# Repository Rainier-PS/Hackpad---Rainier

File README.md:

# Hackpad-Rainier

Hackpad-Rainier is a small 3x3 macropad featuring an encoder, OLED display, LED backlight, and various keymap layers. It is constructed using KMK firmware and the Seeed XIAO RP2040. It is designed to facilitate shortcuts, media management, number entry, and visual feedback for different layers.

## Features

- 3×3 key configuration (9 physical buttons)
- EC11 rotary encoder that includes a push button
- Layer switching through encoder press or key combinations
- OLED display for showing layers and modes
- SK6812 MINI-E LEDs backlight with several brightness settings
- KMK firmware 
- Custom-designed PCB (2-layer) and a 3D-printed case

## Visual Overview

### Assembled Hackpad

>In accordance with the submission requirements, the interior of both the top and bottom parts of the case are branded with my name.

### Schematic

### PCB Layout

## Layer Configuration

### Layer 0 – Shortcuts and Media
| Top Row       | Middle Row     | Bottom Row    |
|---------------|----------------|----------------|
| Media Prev    | Play/Pause     | Media Next     |
| Undo          | Redo           | Save           |
| Copy          | Paste          | Cut            |

Encoder: Volume control (default)  
Encoder button: Toggle between volume, zoom, brightness, and timeline scrubbing

### Layer 1 – Numpad
| Top Row       | Middle Row     | Bottom Row    |
|---------------|----------------|----------------|
| 7             | 8              | 9              |
| 4             | 5              | 6              |
| 1             | 2              | 3              |

Encoder and screen modes remain active.

## Firmware

- Written in Python using KMK firmware
- Supports multiple layers and encoder modes
- Keymap stored in `keymap.py`
- OLED uses SSD1306 I²C (SDA = GP6, SCL = GP7)
- LEDs controlled on GP1
- Fully customizable layout

## BOM: Bill of Materials

| Component                   | Quantity | Notes                                                                 |
|-----------------------------|----------|-----------------------------------------------------------------------|
| MX-Style switches           | 9        | Any MX-style switch (linear/tactile/clicky)                          |
| Blank DSA keycaps (White)   | 9        | Or any compatible keycaps                                            |
| Through-hole 1N4148 Diodes  | 12       | For switch matrix and rotary encoder                                 |
| EC11 rotary encoder         | 1        | With built-in push button                                            |
| 0.91" 128x32 OLED (I²C)     | 1        | SSD1306-compatible (GND/VCC/SCL/SDA)                                 |
| SK6812 MINI-E LEDs          | 16       | For underglow or key backlighting                                    |
| Seeed XIAO RP2040           | 1        | Through-hole version (required for compatibility)                    |
| Custom PCB                  | 1        | 2-layer, ≤100×100mm                                                  |
| 3D Printed Case             | 1        | Two parts: top and bottom                                            |
| M3×5m×4mm heat-set inserts  | 7        | Used for assembly                                                    |
| M3x16mm screws              | 7        | For screwing into inserts                                            |

>This project follows the Hackpad requirements: only approved parts are used,the case is entirely 3D printed, with no non-printed parts involved.

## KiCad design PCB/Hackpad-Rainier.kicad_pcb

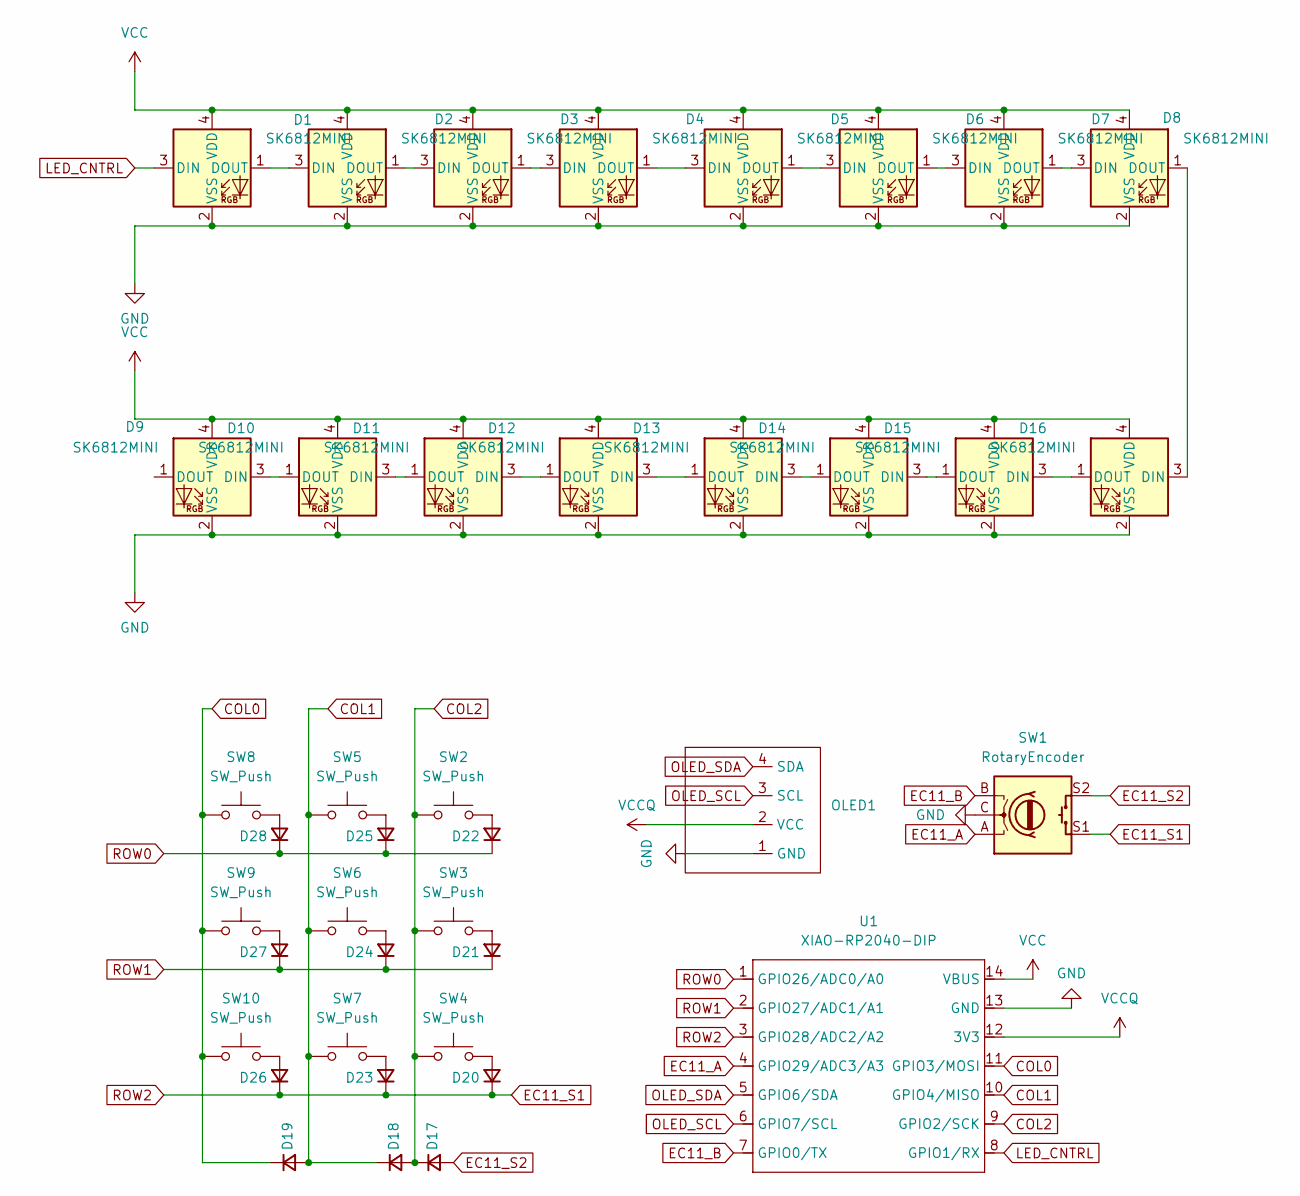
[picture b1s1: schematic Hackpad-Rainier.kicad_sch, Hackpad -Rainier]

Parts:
D1, D2, D3, D4, D5, D6, D7, D8, D9, D10, D11, D12, D13, D14, D15, D16: SK6812MINI; SK6812-MINI-E
D17, D18, D19, D20, D21, D22, D23, D24, D25, D26, D27, D28: D_Small; D_T-1_P5.08mm_Horizontal
OLED1: SSD1306-0.91-OLED-4pin-128x32
SW1: RotaryEncoder; RotaryEncoder_Alps_EC11E-Switch_Vertical_H20mm
SW2, SW3, SW4, SW5, SW6, SW7, SW8, SW9, SW10: SW_Push; SW_Cherry_MX_1.00u_PCB
U1: XIAO-RP2040-DIP

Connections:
COL0: D19.1 (K), SW8.2, SW9.2, SW10.2, U1.11 (GPIO3/MOSI)
COL1: D18.1 (K), D19.2 (A), SW5.2, SW6.2, SW7.2, U1.10 (GPIO4/MISO)
COL2: D17.1 (K), D18.2 (A), SW2.2, SW3.2, SW4.2, U1.9 (GPIO2/SCK)
EC11_A: SW1.A, U1.4 (GPIO29/ADC3/A3)
EC11_B: SW1.B, U1.7 (GPIO0/TX)
EC11_S1: D20.1 (K), D23.1 (K), D26.1 (K), SW1.S1, U1.3 (GPIO28/ADC2/A2)
EC11_S2: D17.2 (A), SW1.S2
GND: D1.2 (VSS), D2.2 (VSS), D3.2 (VSS), D4.2 (VSS), D5.2 (VSS), D6.2 (VSS), D7.2 (VSS), D8.2 (VSS), D9.2 (VSS), D10.2 (VSS), D11.2 (VSS), D12.2 (VSS), D13.2 (VSS), D14.2 (VSS), D15.2 (VSS), D16.2 (VSS), OLED1.1 (GND), SW1.C, U1.13 (GND)
LED_CNTRL: D1.3 (DIN), U1.8 (GPIO1/RX)
unnamed: D1.1 (DOUT), D2.3 (DIN)
unnamed: D2.1 (DOUT), D3.3 (DIN)
unnamed: D3.1 (DOUT), D4.3 (DIN)
unnamed: D4.1 (DOUT), D5.3 (DIN)
unnamed: D5.1 (DOUT), D6.3 (DIN)
unnamed: D6.1 (DOUT), D7.3 (DIN)
unnamed: D7.1 (DOUT), D8.3 (DIN)
unnamed: D10.3 (DIN), D11.1 (DOUT)
unnamed: D9.3 (DIN), D10.1 (DOUT)
unnamed: D11.3 (DIN), D12.1 (DOUT)
unnamed: D12.3 (DIN), D13.1 (DOUT)
unnamed: D13.3 (DIN), D14.1 (DOUT)
unnamed: D14.3 (DIN), D15.1 (DOUT)
unnamed: D15.3 (DIN), D16.1 (DOUT)
unnamed: D8.1 (DOUT), D16.3 (DIN)
unnamed: D20.2 (A), SW4.1
unnamed: D21.2 (A), SW3.1
unnamed: D22.2 (A), SW2.1
unnamed: D23.2 (A), SW7.1
unnamed: D24.2 (A), SW6.1
unnamed: D25.2 (A), SW5.1
unnamed: D26.2 (A), SW10.1
unnamed: D27.2 (A), SW9.1
unnamed: D28.2 (A), SW8.1
OLED_SCL: OLED1.3 (SCL), U1.6 (GPIO7/SCL)
OLED_SDA: OLED1.4 (SDA), U1.5 (GPIO6/SDA)
ROW0: D22.1 (K), D25.1 (K), D28.1 (K), U1.1 (GPIO26/ADC0/A0)
ROW1: D21.1 (K), D24.1 (K), D27.1 (K), U1.2 (GPIO27/ADC1/A1)
VCC: D1.4 (VDD), D2.4 (VDD), D3.4 (VDD), D4.4 (VDD), D5.4 (VDD), D6.4 (VDD), D7.4 (VDD), D8.4 (VDD), D9.4 (VDD), D10.4 (VDD), D11.4 (VDD), D12.4 (VDD), D13.4 (VDD), D14.4 (VDD), D15.4 (VDD), D16.4 (VDD), U1.14 (VBUS)
VCCQ: OLED1.2 (VCC), U1.12 (3V3)

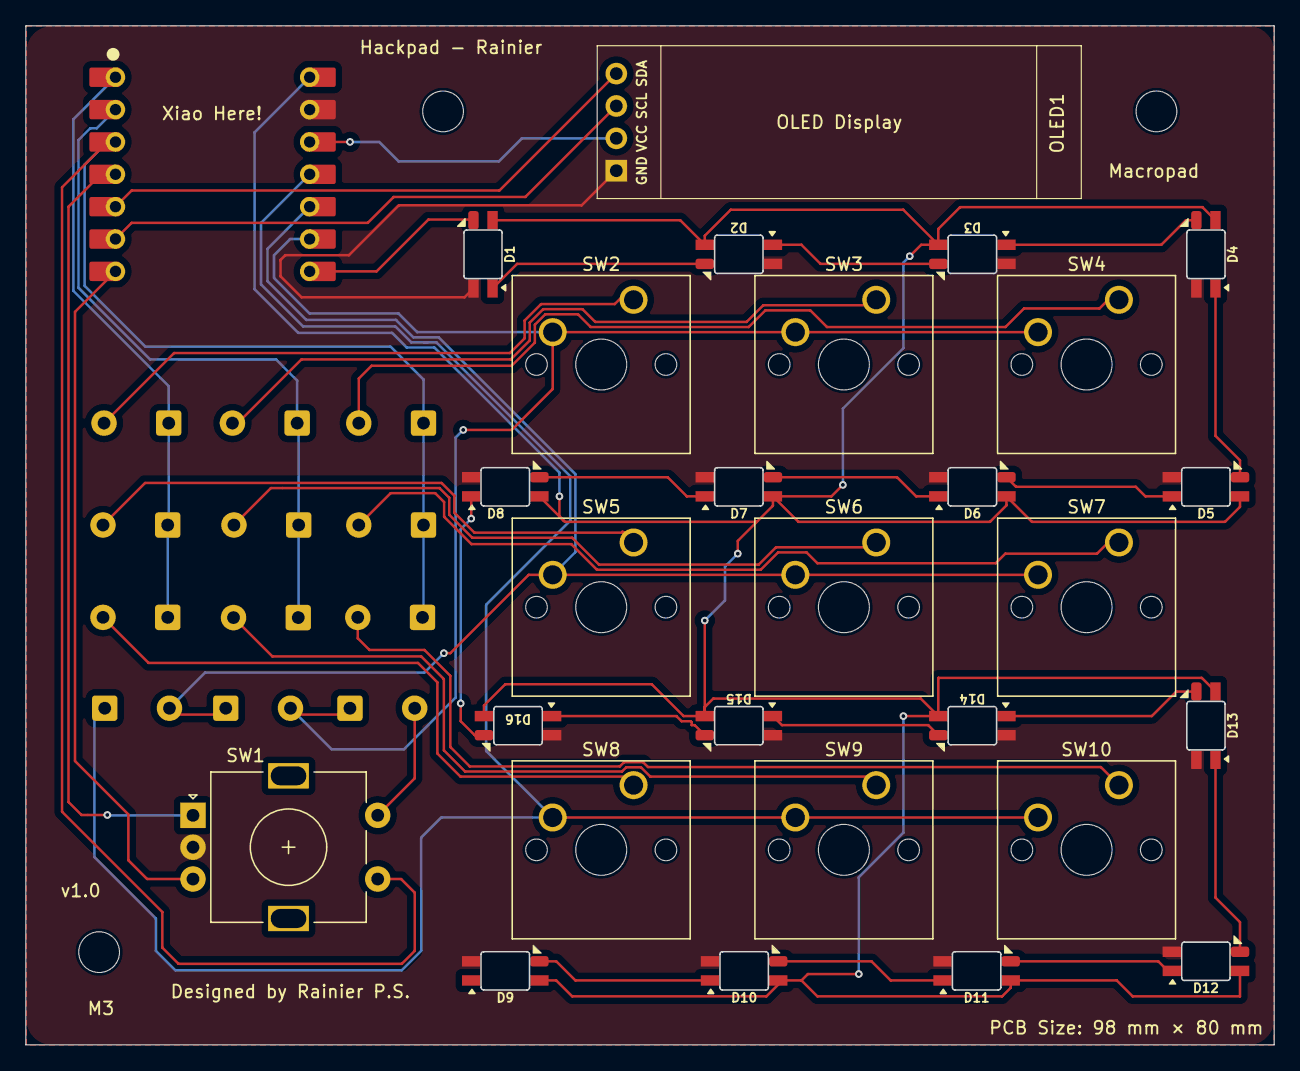
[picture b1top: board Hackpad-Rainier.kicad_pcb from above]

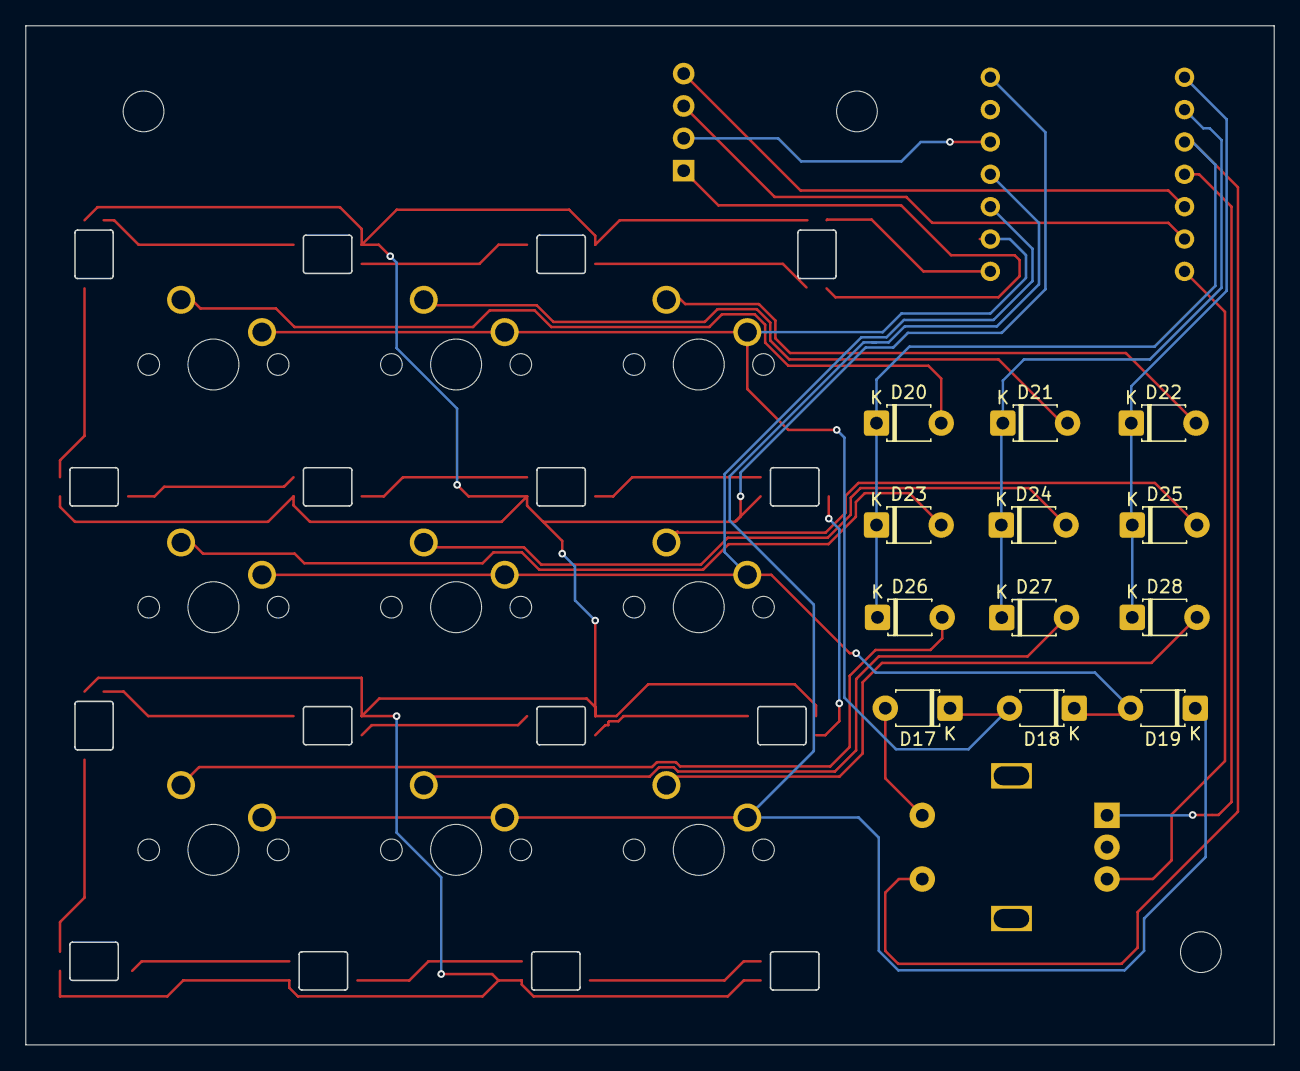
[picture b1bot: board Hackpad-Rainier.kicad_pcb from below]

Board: 2 copper layers, 97.9 x 79.9 mm, 40 parts (12 on the bottom side), 39 nets.

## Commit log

2025-07-02 Create Temp
